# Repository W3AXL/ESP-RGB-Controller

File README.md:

# ESP-RGB-Controller
Tiny ESP8266-based RGB LED controller

## Board Hardware
*Located in the root directory*

Included is the kicad project for the PCB. It's very simple and requires minimal parts. An included BOM.txt gives part numbers used for my assemblies. However, feel free to substitute parts as you see fit.

## Board Firmware
*Located in the SW-Arduino Directory*

The MCU is an AtMega328P in 32-TQFP package. **You will need an ISP tool to flash the firmware, such as a [USBTinyISP](https://learn.adafruit.com/usbtinyisp) or an [Arduino flashed as an ISP](https://www.arduino.cc/en/Tutorial/BuiltInExamples/ArduinoISP).**

The firmware was designed to run on the [Minicore Arduino platform](https://github.com/MCUdude/MiniCore). You will need to add this to your boards manager and install it in your Arduino IDE. The following settings are used to compile and flash the firmware:

* Board: AtMega328
* Clock: Internal 8MHz
* BOD: 2.7V
* EEPROM: EEPROM retained
* Compiler LTO: LTO Disabled
* Variant: 328P/PA
* Bootloader: No Bootloader

You will also need the WifiEspAt library for Arduino, and will need to edit the Wifi login credentials to match your wifi network. Otherwise, it should be plug and play with up-to-date ESP-01 modules.

**Note: You will need to update your ESP-01 modules to AT version 2.1 or greater. See [the following page on firmware versions from the WifiESPAt library](https://github.com/jandrassy/WiFiEspAT#at-firmware-versions)**

A minor overview of the features of this firmware:
* Recalls last state on power-up, useful if power is interrupted
* Reports the current setting in a small webpage when the GET request is recieved, useful for status checking

## Control the lights!
### GET Requests
The simplest method of control is through your browser, with a simple HTTP GET request like so:
```
http://<ip.address>?rgb=255,255,255
```
This will set all three color channels to full brightness.
### Controller App
*Locategd in SW-TrayTool*

You can build the C# Windows Forms app for a slightly more robust control system. The tool includes provisions for multiple controllers and presets, as well as a tray icon for controlling lights in a nice clean way.

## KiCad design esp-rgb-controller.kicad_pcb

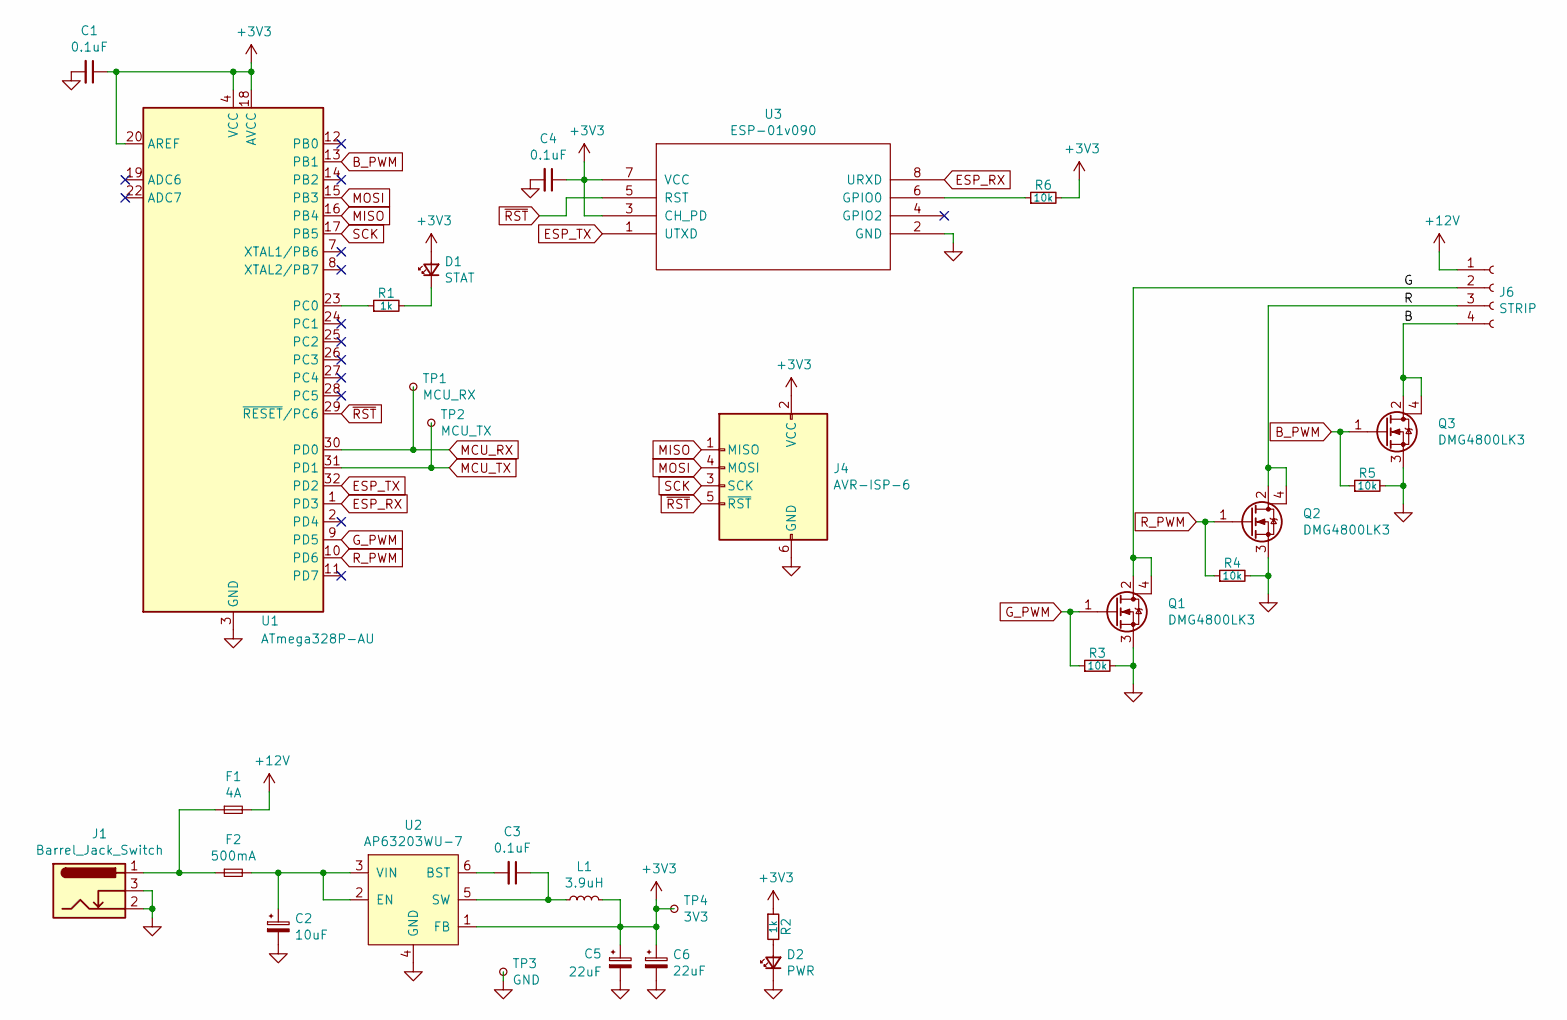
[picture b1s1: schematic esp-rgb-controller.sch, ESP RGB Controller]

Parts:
C1, C3, C4: 0.1uF; C_0805_2012Metric_Pad1.15x1.40mm_HandSolder
C2: 10uF; CP_EIA-3528-15_AVX-H_Pad1.50x2.35mm_HandSolder
C5, C6: 22uF; CP_EIA-3528-15_AVX-H_Pad1.50x2.35mm_HandSolder
D1: STAT; LED_0805_2012Metric_Pad1.15x1.40mm_HandSolder
D2: PWR; LED_0805_2012Metric_Pad1.15x1.40mm_HandSolder
F1: 4A; Fuse_1206_3216Metric_Pad1.42x1.75mm_HandSolder
F2: 500mA; Fuse_1206_3216Metric_Pad1.42x1.75mm_HandSolder
J1: Barrel_Jack_Switch; BarrelJack_CUI_PJ-102AH_Horizontal
J4: AVR-ISP-6; PinHeader_2x03_P2.54mm_Vertical_SMD
J6: STRIP; TerminalBlock_bornier-4_P5.08mm
L1: 3.9uH; L_Bourns-SRN6028
Q1, Q2, Q3: DMG4800LK3; TO-252-3_TabPin4
R1, R2: 1k; R_0805_2012Metric_Pad1.15x1.40mm_HandSolder
R3, R4, R5, R6: 10k; R_0805_2012Metric_Pad1.15x1.40mm_HandSolder
TP1: MCU_RX; TestPoint_Pad_D1.0mm
TP2: MCU_TX; TestPoint_Pad_D1.0mm
TP3: GND; TestPoint_Pad_D1.0mm
TP4: 3V3; TestPoint_Pad_D1.0mm
U1: ATmega328P-AU; TQFP-32_7x7mm_P0.8mm
U2: AP63203WU-7; TSOT-23-6_HandSoldering
U3: ESP-01v090; ESP-01

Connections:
+3V3: C1.1, C4.1, C5.1, C6.1, D1.2 (A), J4.2 (VCC), L1.2, R2.1, R6.2, TP4.1, U1.4 (VCC), U1.6 (VCC), U1.18 (AVCC), U1.20 (AREF), U2.1 (FB), U3.3 (CH_PD), U3.7 (VCC)
+12V: F1.2, J6.1
/B: J6.4, Q3.2 (D), Q3.4 (D)
/G: J6.2, Q1.2 (D), Q1.4 (D)
/R: J6.3, Q2.2 (D), Q2.4 (D)
B_PWM: Q3.1 (G), R5.1, U1.13 (PB1)
ESP_RX: U1.1 (PD3), U3.8 (URXD)
ESP_TX: U1.32 (PD2), U3.1 (UTXD)
GND: C1.2, C2.2, C4.2, C5.2, C6.2, D2.1 (K), J1.2, J1.3, J4.6 (GND), Q1.3 (S), Q2.3 (S), Q3.3 (S), R3.2, R4.2, R5.2, TP3.1, U1.3 (GND), U1.5 (GND), U1.21 (GND), U2.4 (GND), U3.2 (GND)
G_PWM: Q1.1 (G), R3.1, U1.9 (PD5)
MCU_RX: TP1.1, U1.30 (PD0)
MCU_TX: TP2.1, U1.31 (PD1)
MISO: J4.1 (MISO), U1.16 (PB4)
MOSI: J4.4 (MOSI), U1.15 (PB3)
unnamed: C2.1, F2.2, U2.2 (EN), U2.3 (VIN)
unnamed: C3.1, L1.1, U2.5 (SW)
unnamed: C3.2, U2.6 (BST)
unnamed: D1.1 (K), R1.2
unnamed: D2.2 (A), R2.2
unnamed: F1.1, F2.1, J1.1
unnamed: R1.1, U1.23 (PC0)
unnamed: R6.1, U3.6 (GPIO0)
R_PWM: Q2.1 (G), R4.1, U1.10 (PD6)
SCK: J4.3 (SCK), U1.17 (PB5)
~RST: J4.5 (~RST), U1.29 (~RESET~/PC6), U3.5 (RST)

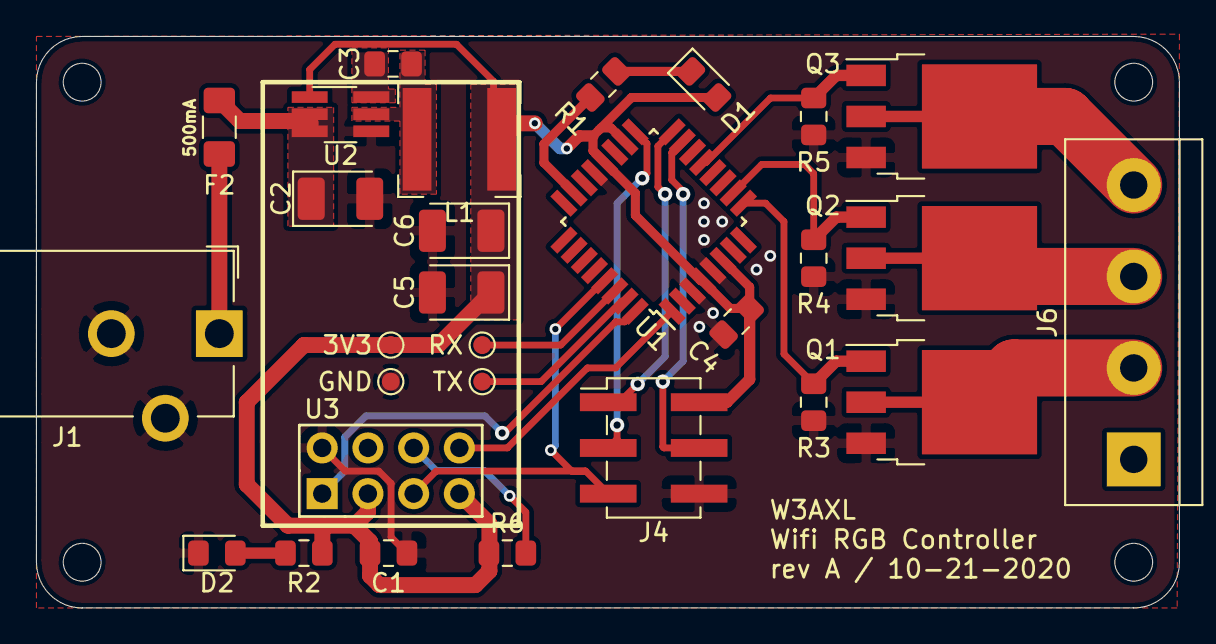
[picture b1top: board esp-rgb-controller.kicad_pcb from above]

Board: 2 copper layers, 63.5 x 31.8 mm, 30 parts (1 on the bottom side), 25 nets.

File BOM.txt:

Qty   | Desc	      		      | Ref	      | P/N
----------------------------------------------------------------------
2	22uF Tant Cap, SMD 1411		C5,C6		‎TAJB226K020RNJ‎
1	10uF Tant Cap, SMD 1411		C2		‎TAJB106K020RNJ‎
1	3.3V Buck Regulator, TSOT26	U2		AP63203WU-7
1	ATMega328P-AU TQFP-32		U1		‎ATMEGA328P-AU
1	2mm x 5.5mm DC Barrel Jack	J1		PJ-102AH
3	0.1uF Ceramic Cap, SMD 0805	C1,C3,C4	CL21B104KACNNNC‎
1	3.9uH Inductor SMD 6x6mm	L1		‎ASPI-0628-3R9M-T1
1	Blue LED SMD 0805		STAT		150080BS75000‎
1	Red LED SMD 0805		PWR		150080RS75000
1	500mA Fuse SMD 1206		F2		C1F 500
1	4A Fuse SMD 1206		F1		C1F 4
1	02x03 0.1" ISP Header SMD	J4		10129383-906001ALF
1	4-Pos Screw Terminal 0.2" THT	J6		Eb21A-04-D
3	N-CH MOSFET 10A 30V SMD TO252	Q1,Q2,Q3	‎DMG4800LK3-13
2	1kOhm Resistor SMD 0805		R1,R2		RNCP0805FTD1K00‎
4	10kOhm Resistor SMD 0805	R3,R4,R5,R6	‎RNCP0805FTD10K0
1	02x04 0.1" ESP-01 Socket	U3		‎RS2-08-G‎

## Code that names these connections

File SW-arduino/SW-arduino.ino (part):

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#include <WiFiEspAT.h>
#include <EEPROM.h>

#define RPIN    PD6
#define GPIN    PD5
#define BPIN    PB1
#define STATPIN PC0

#define RXPIN   PD2
#define TXPIN   PD3

#define COL_WARM_WHITE_R 255
#define COL_WARM_WHITE_G 75
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}

/** 
 * @brief initializes OSC1 for PWM on pin PB1
 */
void pwmInitOSC1A() {
    // Init pin PB1 as output
    DDRB |= B00000010;
    // OSC1 PWM Init
    TCCR1A |= (1<<COM1A1)|(1<<WGM10);    // OCR1A in normal mode, phase-corrected PWM
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    Serial.println("");
    Serial.println("");
    Serial.println("Starting up");
    // initialize PD5&6
    pinMode(RPIN,OUTPUT);
    pinMode(GPIN,OUTPUT);
    // initialize PC0
    DDRC |= B00000001;
    statLed(false);
    // initialize PB1
    pwmInitOSC1A();
    // start ESP serial
    esp.begin(9600);
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
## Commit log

2020-10-19 initial schematic work
2020-10-19 initial PCB work
2020-10-20 more PCB work
2020-10-21 more schematic + pcb work
2020-10-22 finished up design, ordered
2020-10-31 finished code for arduino
2020-10-31 removed unused ESP SW
2020-11-01 more work on windows app
2020-11-01 more work on controller app
2020-11-02 basic control app fully working
2020-11-02 removed bin folder and added gitignore
2020-11-02 added tray icon functionality
2020-11-02 fixed some errors with tray icon
2020-11-02 added board image
2020-11-02 added more images
2020-11-02 added BOM
2020-11-02 updated icons
